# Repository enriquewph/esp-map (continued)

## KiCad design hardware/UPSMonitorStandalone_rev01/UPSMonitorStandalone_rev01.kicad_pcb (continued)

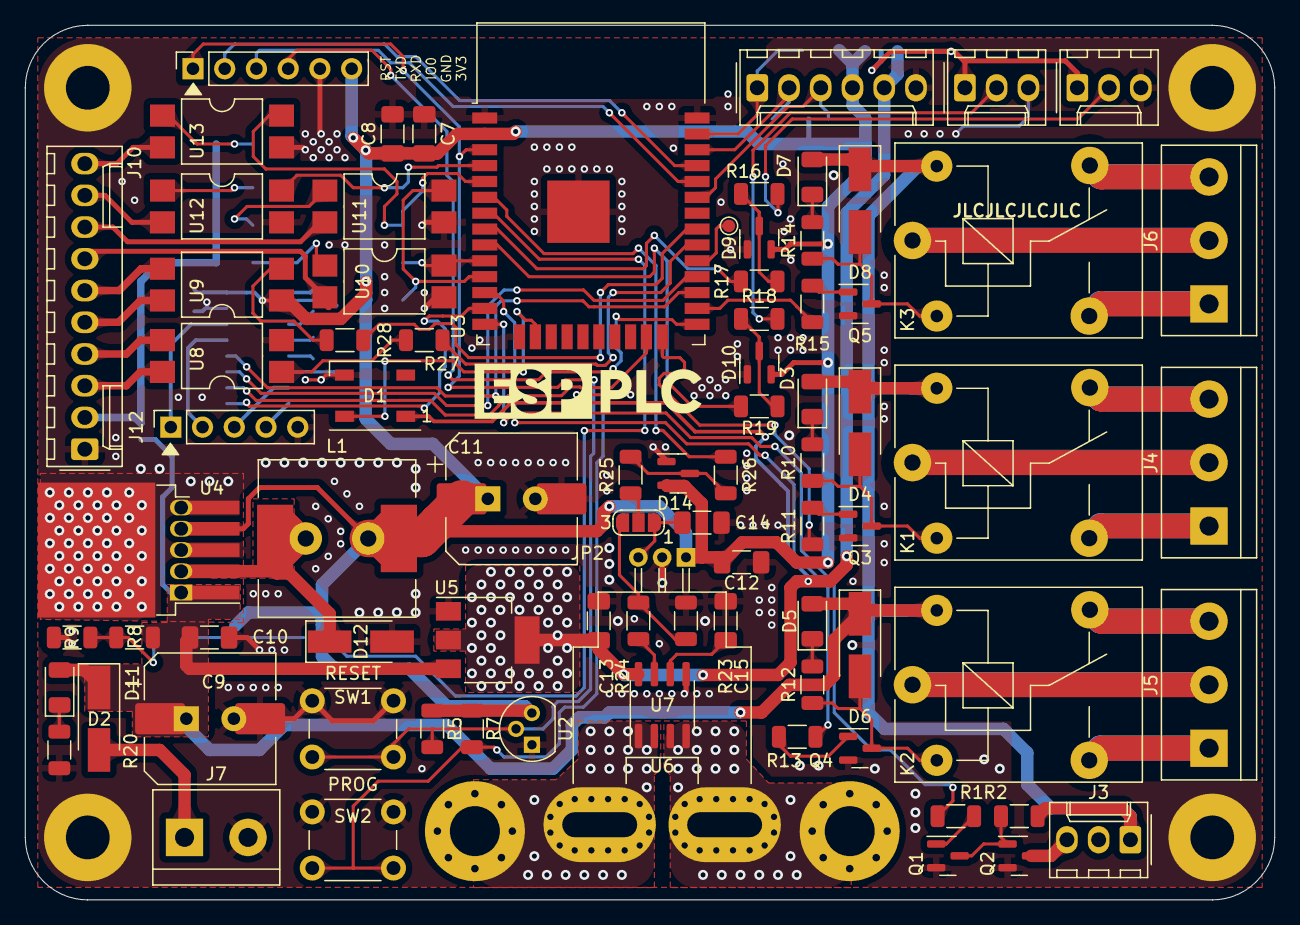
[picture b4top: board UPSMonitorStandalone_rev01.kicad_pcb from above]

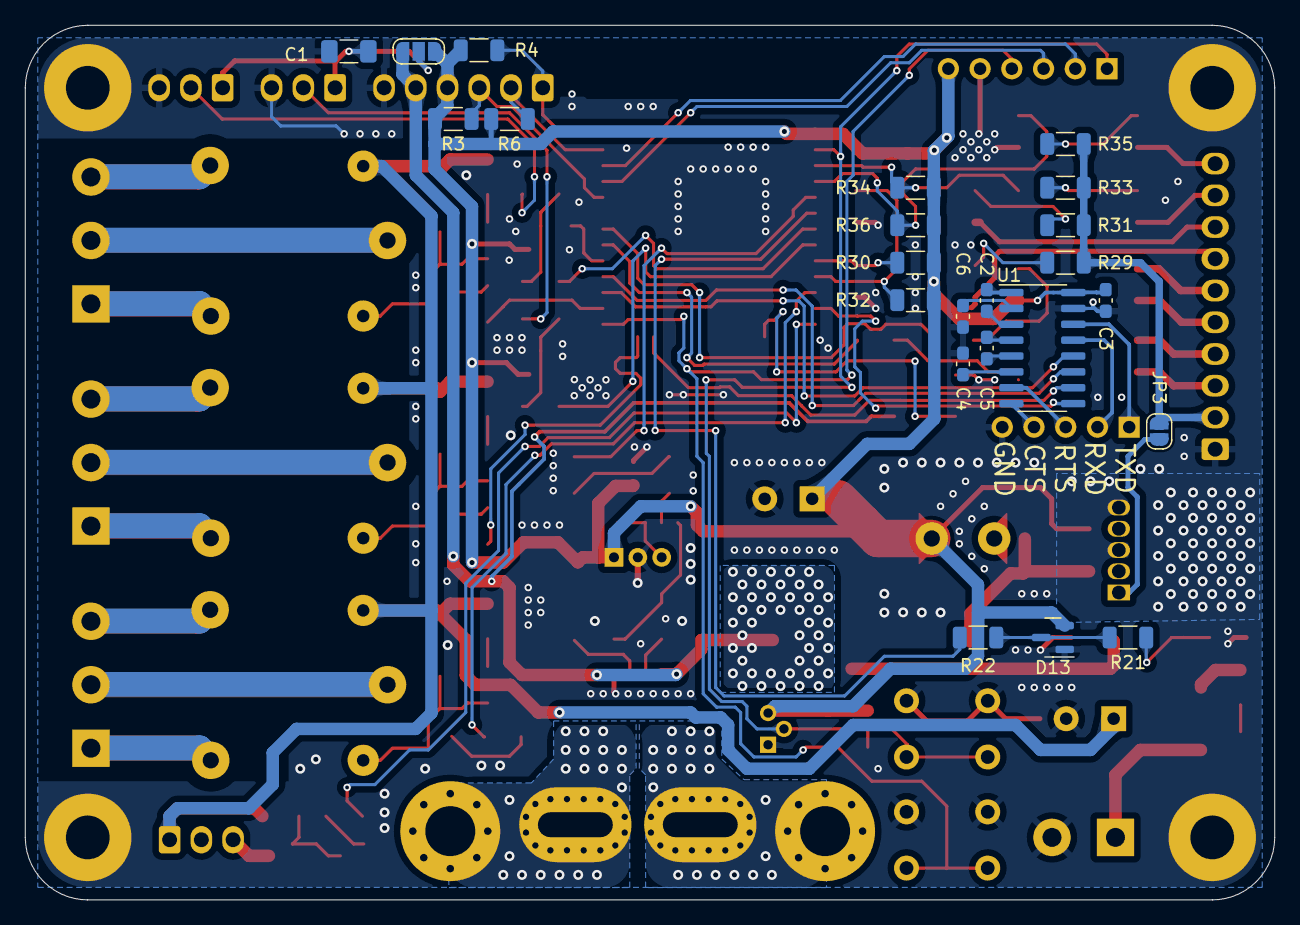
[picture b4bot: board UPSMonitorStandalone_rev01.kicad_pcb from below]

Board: 2 copper layers, 100.0 x 70.0 mm, 106 parts (23 on the bottom side), 95 nets.

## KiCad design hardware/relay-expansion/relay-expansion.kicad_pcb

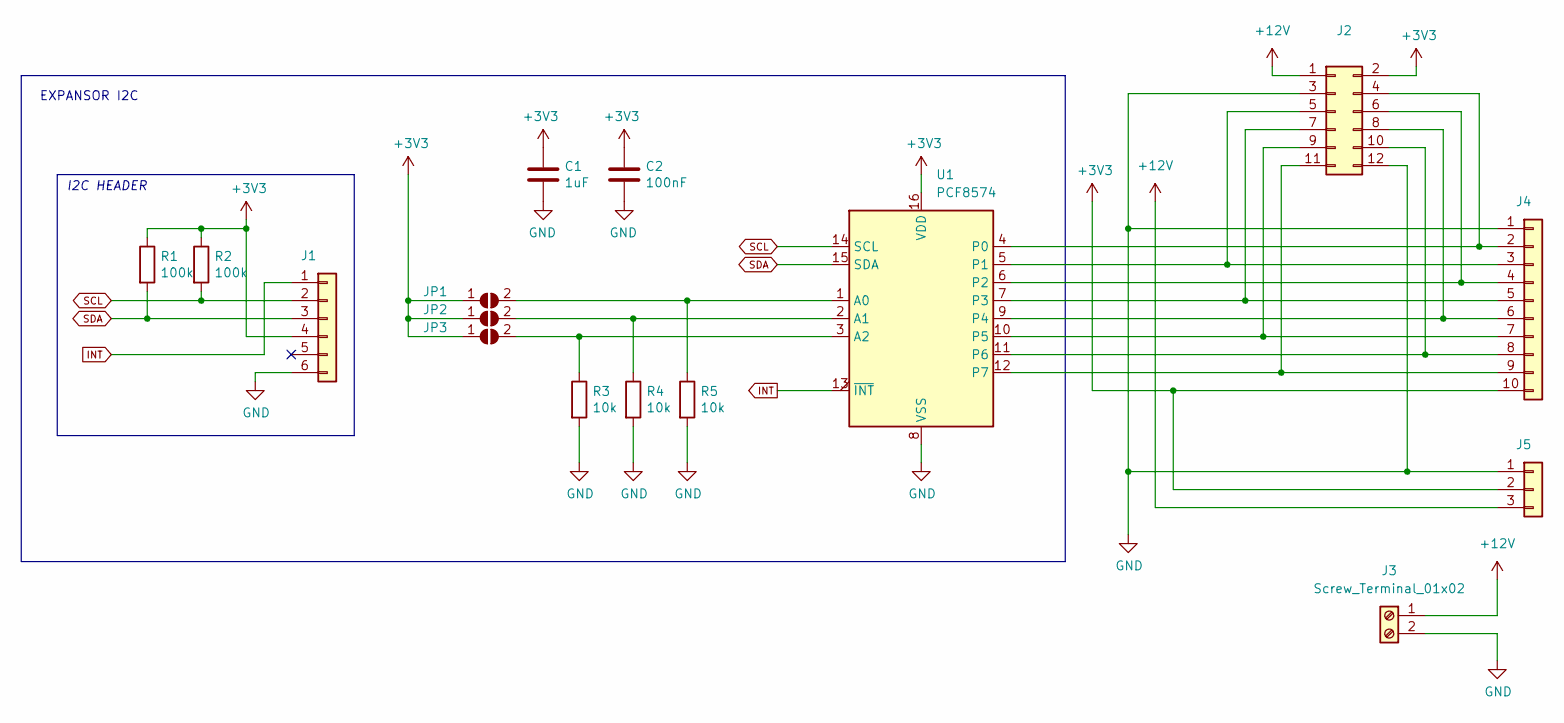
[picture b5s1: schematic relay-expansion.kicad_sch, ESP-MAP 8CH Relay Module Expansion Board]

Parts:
C1: 1uF; C_1206_3216Metric_Pad1.33x1.80mm_HandSolder; Voltage 50V
C2: 100nF; C_1206_3216Metric_Pad1.33x1.80mm_HandSolder; Voltage 50V
J1: Conn_01x06; Molex_KK-254_AE-6410-06A_1x06_P2.54mm_Vertical
J2: Conn_02x06_Odd_Even; PinHeader_2x06_P2.54mm_Vertical
J3: Screw_Terminal_01x02; TerminalBlock_bornier-2_P5.08mm
J4: Conn_01x10; PinSocket_1x10_P2.54mm_Vertical
J5: Conn_01x03; PinSocket_1x03_P2.54mm_Vertical
JP1, JP2, JP3: SolderJumper_2_Open; SolderJumper-2_P1.3mm_Open_RoundedPad1.0x1.5mm
R1, R2: 100k; R_1206_3216Metric
R3, R4, R5: 10k; R_1206_3216Metric
U1: PCF8574; SOIC-16W_7.5x10.3mm_P1.27mm

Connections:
+3V3: C1.1, C2.1, J1.4, J2.2, J4.10, J5.2, JP1.1 (A), JP2.1 (A), JP3.1 (A), R1.1, R2.1, U1.16 (VDD)
+12V: J2.1, J3.1, J5.3
GND: C1.2, C2.2, J1.6, J2.3, J2.12, J3.2, J4.1, J5.1, R3.2, R4.2, R5.2, U1.8 (VSS)
INT: J1.1, U1.13 (~INT)
unnamed: J2.4, J4.2, U1.4 (P0)
unnamed: J2.5, J4.3, U1.5 (P1)
unnamed: J2.6, J4.4, U1.6 (P2)
unnamed: J2.7, J4.5, U1.7 (P3)
unnamed: J2.8, J4.6, U1.9 (P4)
unnamed: J2.9, J4.7, U1.10 (P5)
unnamed: J2.10, J4.8, U1.11 (P6)
unnamed: J2.11, J4.9, U1.12 (P7)
unnamed: JP1.2 (B), R5.1, U1.1 (A0)
unnamed: JP2.2 (B), R4.1, U1.2 (A1)
unnamed: JP3.2 (B), R3.1, U1.3 (A2)
SCL: J1.2, R2.2, U1.14 (SCL)
SDA: J1.3, R1.2, U1.15 (SDA)

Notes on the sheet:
EXPANSOR I2C
I2C HEADER

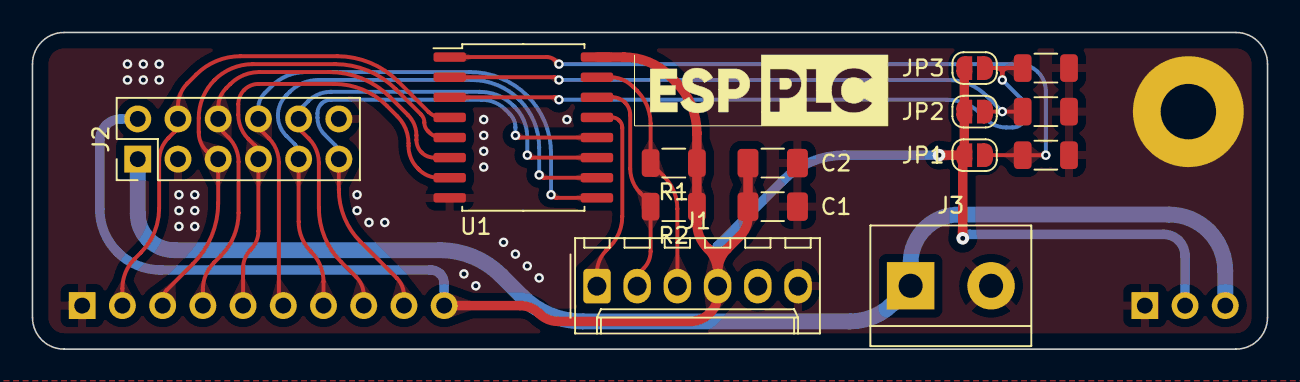
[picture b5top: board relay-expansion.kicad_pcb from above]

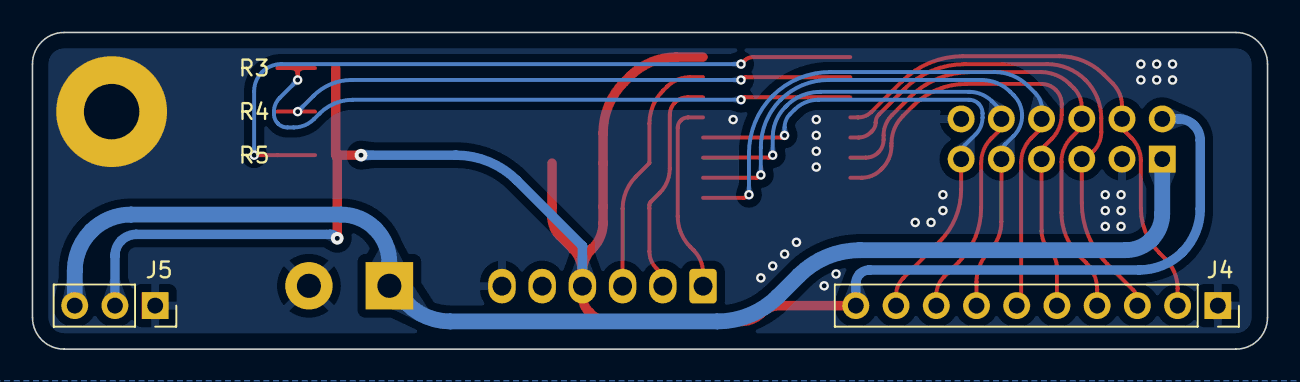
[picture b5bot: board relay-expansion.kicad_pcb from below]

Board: 2 copper layers, 78.0 x 20.0 mm, 16 parts (2 on the bottom side), 17 nets.

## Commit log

2024-01-07 Repo Migration
    Migrate repo from ESP-PLC & rebranding to ESP-MAP
2024-01-07 add social preview image
2024-01-07 Start Control Module project
2024-01-07 Update issue templates
2024-01-20 AS OF 20/1/2024
2024-11-21 add some new PCB's
2024-11-25 work on lora gateway
2024-11-26 pcb design in progress
2024-11-26 add sd card footprint
